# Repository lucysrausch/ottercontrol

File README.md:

# OtterControl
Hardware files for OtterControl BLDC motor controller.

## What is OtterControl?
OtterControl is a open source, open hardware DC / BLDC motor controller.
The basic idea was to make the well-known VESC (http://vedder.se/2015/01/vesc-open-source-esc/) even cheaper - making hoverboard-powered armchairs or crazycarts affordable.

While these 350W hoverboards motors are great and quiet affordable (only 40€ in Germany),
you need a powerful ESC to get them running. Until now, the only open ESC I'm aware of is the VESC - which is great and all, but with ~100-120€ per piece quiet expensive.
That's why I decided to save on some parts:

* Single-Chip Gatedrivers
* Mosfets in D2PAK package
* Chinese HV buck converter
* STM32f3 instead of f4: still powerful enough, and with more internal analog peripherals

The STM32f303 has lots of internal peripherals such as OpAmps, PGAs etc.
Using this chip reduces external components and system complexity - saving about 10€.
Also, using D2PAK Mosfets allows more flexible part selection - saving another 20€ with almost the same specs.

The final BOM for 50pcs of OtterControl turns out to be ~19€ per piece.

## Specs
* max. 50A continous motor current (~90A peak)
* max. 80V (with 63V capacitors = 14S LiIon)
* STMBL Codebase ("easy to use", configurable)
* no additional programming device (USB DFU support)

* UART, RS485, CAN, USB
* PPM (to be implemented)

* 3 GPIOs, sharing one Timer (eg. as hall sensor input, quadrature encoder)
* 5V max. 200mA out (eg. for hall sensors)
* Otter

## Versions

There are currently two different versions of OtterControl V1.3:
One with 1mOhm current-sensing shunts, and one with 3mOhm.
The reason for this:

To measure the phase current, the f303 internal PGA is set to 16x gain.
This gives a input range of 3.2AVDD / 16 = 200mV.
It is necessary to measure positiv and negative currents, so the shunt is pre-biased to 100mV, giving +/- 100mV measurable voltage drop.

* With 1mOhm, this means 100A full scale
* With 3mOhm, this means 33A full scale

Depending on your application, you want as much current resolution as possible.
For a 5A DC motor, or a small BLDC, 33A is way enough, archiving good current regulation.
However, for applications with more current, 1mOhm increases the current scale to the necessary range.

## Software

OtterControl is based on the stmbl codebase (https://github.com/rene-dev/stmbl).
A ported version can be found in my fork (ottercontrol branch).
Essentially, the code on the f303 is the same as in stmbl, but without the f4 this mcu now also handles encoder input, position regulation, user settings etc.

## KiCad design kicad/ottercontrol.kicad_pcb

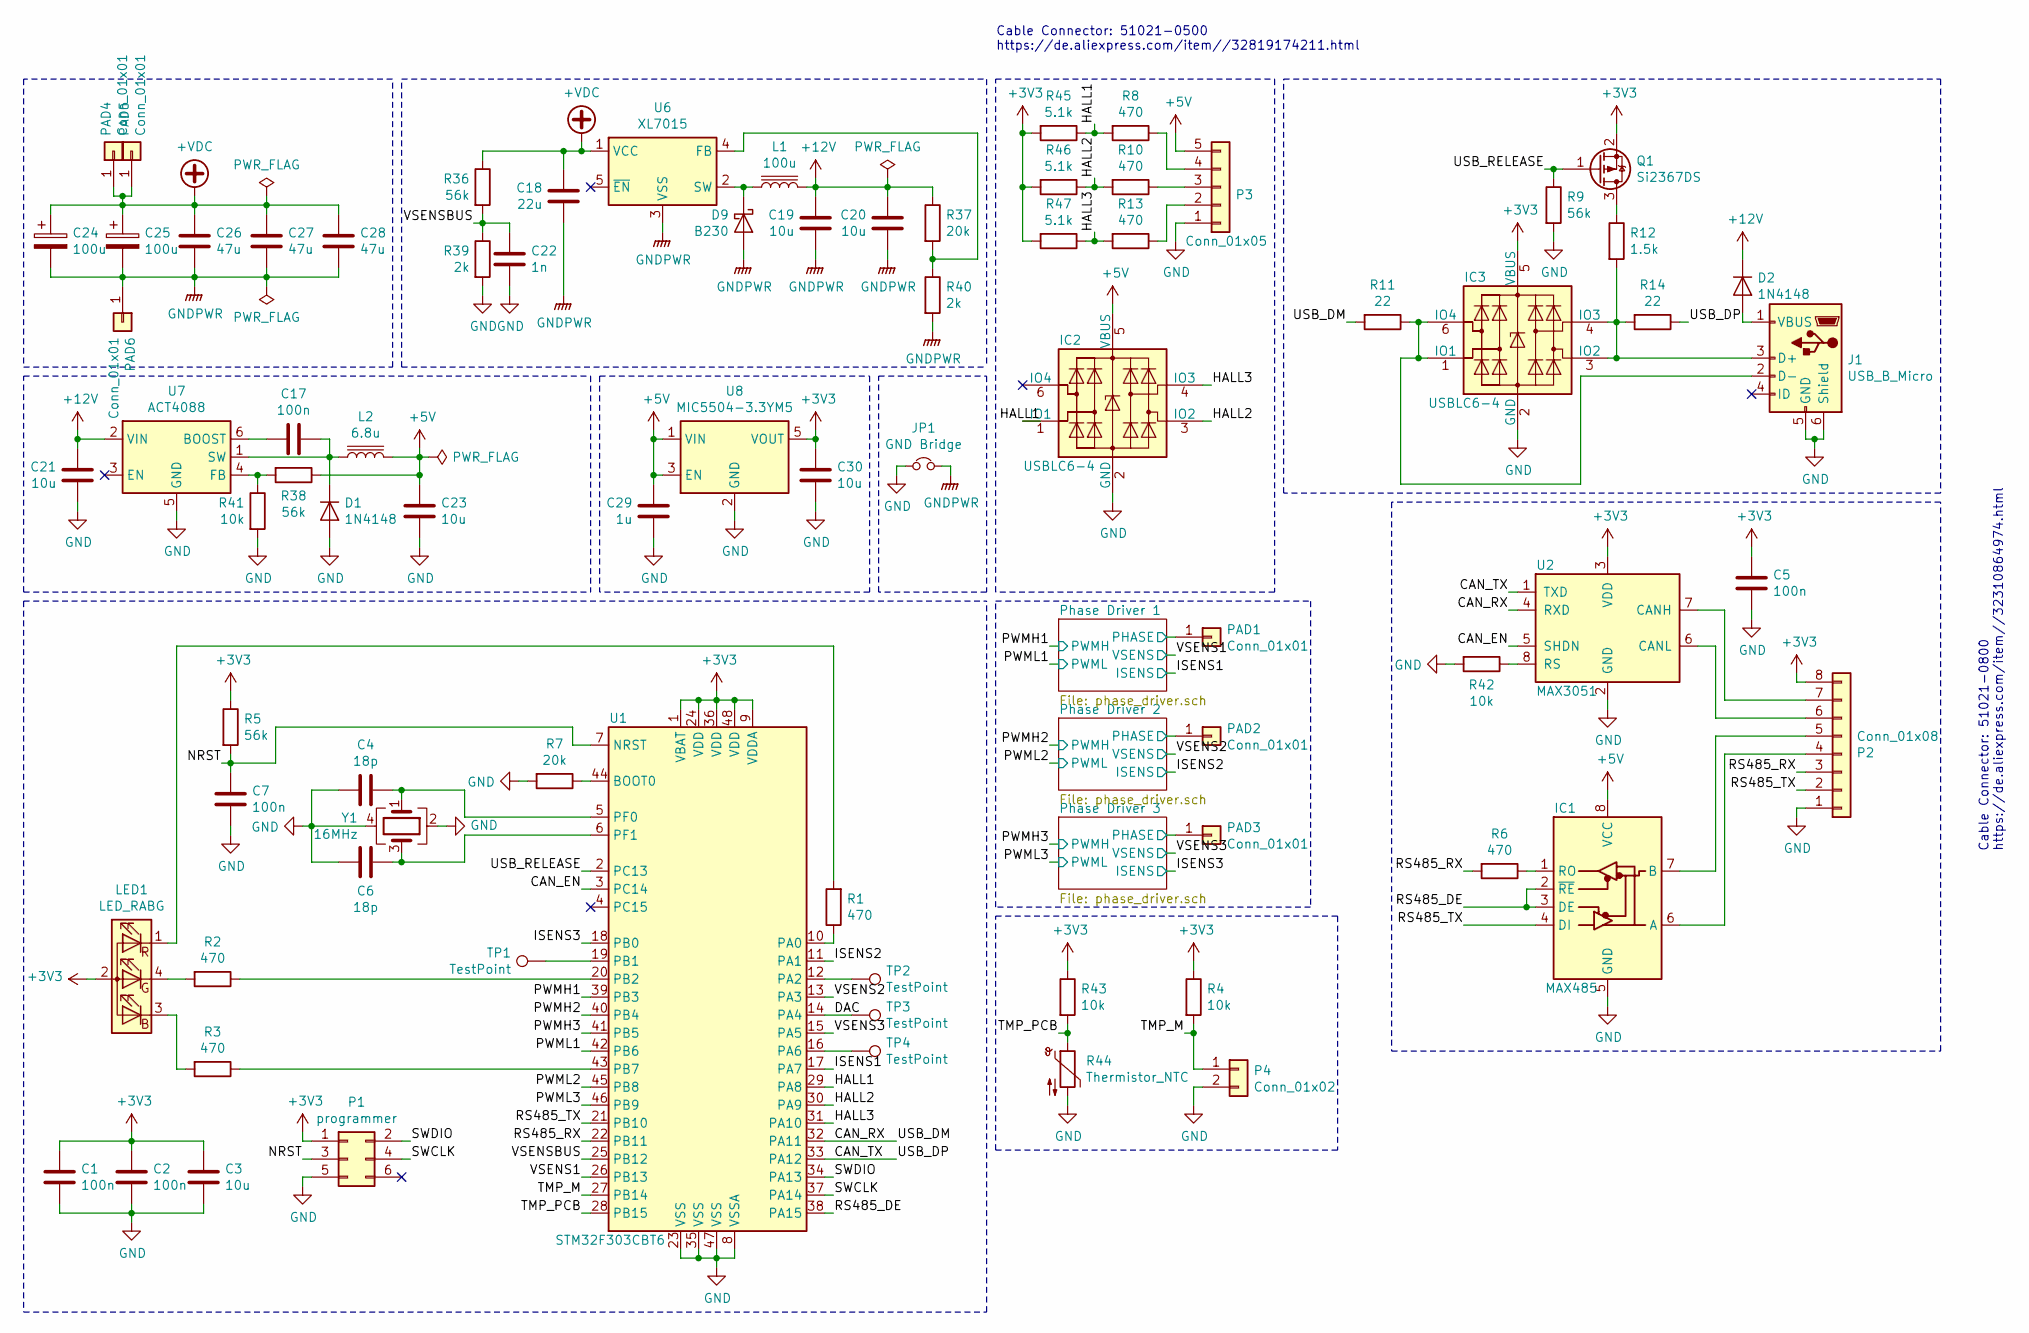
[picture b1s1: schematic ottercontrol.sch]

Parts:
C1, C2, C5, C7: 100n; C_0603_1608Metric; Voltage Rating DC 25; MPN GRM033C81E104KE14E
C3, C23, C30: 10u; C_0603_1608Metric; Voltage Rating DC 6.3; MPN JMK107ABJ106MA-T
C4, C6: 18p; C_0603_1608Metric; Tolerance 1%; MPN GRM0335C1E180FA01D
C17: 100n; C_0603_1608Metric; Voltage Rating DC 50; MPN CC0603MRY5V9BB104
C18: 22u; C_2220_5650Metric; Voltage Rating DC 100; MPN C5750X7R1E226M250KA
C19, C20, C21: 10u; C_1206_3216Metric; Voltage Rating DC 25; MPN TMK316BJ106KL-T
C22: 1n; C_0603_1608Metric; Voltage Rating DC 50; MPN 885012206083
C24, C25: 100u; CP_Radial_D12.5mm_P5.00mm; Voltage Rating DC 100; MPN 107CKS100MLQ
C26, C27, C28: 47u; C_2220_5650Metric; Voltage Rating DC 100; MPN CGA9N3X7R1E476M230KB
C29: 1u; C_0603_1608Metric; Voltage Rating DC 25; MPN 885012106022
D1, D2: 1N4148; D_SOD-323F; MPN 1N4148WS
D9: B230; D_SMA; MPN B230AE-13
IC1: MAX485; SOIC-8_3.9x4.9mm_P1.27mm; MPN MAX485CSA+
IC2, IC3: USBLC6-4; SOT-23-6; MPN USBLC6-4SC6
J1: USB_B_Micro; USB_Micro-B_Molex-105017-0001; MPN 105017-0001
JP1: GND Bridge; SolderJumper-2_P1.3mm_Bridged_Pad1.0x1.5mm; MPN n/a
L1: 100u; L_Coilcraft_LPS6235; MPN LPS6235-104MRC
L2: 6.8u; L_Coilcraft_LPS6235; MPN LPS6235-682MRC
LED1: LED_RABG; LED_Avago_PLCC4_3.2x2.8mm_CW
P1: programmer; Tag-Connect_TC2030-IDC-NL_2x03_P1.27mm_Vertical; MPN TC2030-MCP-NL
P2: Conn_01x08; Molex_PicoBlade_53261-0871_1x08-1MP_P1.25mm_Horizontal; MPN 53261-0871
P3: Conn_01x05; Molex_PicoBlade_53261-0571_1x05-1MP_P1.25mm_Horizontal; MPN 53261-0571
P4: Conn_01x02; PinHeader_1x02_P2.54mm_Vertical; MPN n/a
PAD1, PAD2, PAD3, PAD4, PAD5, PAD6: Conn_01x01; TestPoint_THTPad_4.0x4.0mm_Drill2.0mm; MPN n/a
Q1: Si2367DS; SOT-23; MPN SI2367DS-T1-GE3
R1, R2, R3, R6, R8, R10, R13: 470; R_0603_1608Metric; MPN RC0603FR-07100RL
R4, R41, R42, R43: 10k; R_0603_1608Metric; MPN RC0603FR-0710KL
R5, R9, R36, R38: 56k; R_0603_1608Metric; MPN RC0603FR-0756KL
R7, R37: 20k; R_0603_1608Metric; MPN RC0603FR-0720KL
R11, R14: 22; R_0603_1608Metric; MPN RC0603FR-0722RL
R12: 1.5k; R_0603_1608Metric; MPN RC0603FR-071K5L
R39, R40: 2k; R_0603_1608Metric; MPN RC0603FR-072KL
R44: Thermistor_NTC; R_0603_1608Metric; MPN 103AT
R45, R46, R47: 5.1k; R_0603_1608Metric; MPN RC0603FR-075K1L
TP1, TP2, TP3, TP4: TestPoint; TestPoint_Pad_D1.0mm; MPN n/a
U1: STM32F303CBT6; LQFP-48_7x7mm_P0.5mm; MPN STM32F303CBT6
U2: MAX3051; SOIC-8_3.9x4.9mm_P1.27mm; MPN MAX3051ESA+
U6: XL7015; TO-252-5_TabPin3; MPN XL7015
U7: ACT4088; TSOT-23-6; MPN ACT4088US-T
U8: MIC5504-3.3YM5; SOT-23-5; MPN MIC5504-3.3YM5-TR
Y1: 16MHz; Crystal_SMD_3225-4Pin_3.2x2.5mm; MPN FA-238 16.0000MB-K3

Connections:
+3V3: C1.1, C2.1, C3.1, C5.1, C30.1, IC3.5 (VBUS), LED1.2 (A), P1.1, P2.8, Q1.2 (S), R4.1, R5.1, R43.1, R45.2, R46.2, R47.2, U1.1 (VBAT), U1.9 (VDDA), U1.24 (VDD), U1.36 (VDD), U1.48 (VDD), U2.3 (VDD), U8.5 (VOUT); also elsewhere on the board
+5V: C23.1, C29.1, IC1.8 (VCC), IC2.5 (VBUS), L2.2, P3.5, R38.1, U8.1 (VIN), U8.3 (EN)
+12V: C19.1, C20.1, C21.1, D2.1 (K), L1.2, R37.1, U7.2 (VIN); also elsewhere on the board
+VDC: C18.1, C24.1, C25.1, C26.1, C27.1, C28.1, PAD4.1, PAD5.1, R36.1, U6.1 (VCC); also elsewhere on the board
/CAN_EN: U1.3 (PC14), U2.5 (SHDN)
/CAN_RX: R11.2, U1.32 (PA11), U2.4 (RXD)
/CAN_TX: R14.1, U1.33 (PA12), U2.1 (TXD)
/DAC: TP3.1, U1.14 (PA4)
/HALL1: IC2.1 (IO1), R8.2, R45.1, U1.29 (PA8)
/HALL2: IC2.3 (IO2), R10.2, R46.1, U1.30 (PA9)
/HALL3: IC2.4 (IO3), R13.2, R47.1, U1.31 (PA10)
/ISENS1: U1.17 (PA7); also elsewhere on the board
/ISENS2: U1.11 (PA1); also elsewhere on the board
/ISENS3: U1.18 (PB0); also elsewhere on the board
/NRST: C7.1, P1.3, R5.2, U1.7 (NRST)
/PWMH1: U1.39 (PB3); also elsewhere on the board
/PWMH2: U1.40 (PB4); also elsewhere on the board
/PWMH3: U1.41 (PB5); also elsewhere on the board
/PWML1: U1.42 (PB6); also elsewhere on the board
/PWML2: U1.45 (PB8); also elsewhere on the board
/PWML3: U1.46 (PB9); also elsewhere on the board
/Phase Driver 1/PHASE: PAD1.1; also elsewhere on the board
/Phase Driver 2/PHASE: PAD2.1; also elsewhere on the board
/Phase Driver 3/PHASE: PAD3.1; also elsewhere on the board
/RS485_DE: IC1.2 (~RE), IC1.3 (DE), U1.38 (PA15)
/RS485_RX: P2.3, R6.2, U1.22 (PB11)
/RS485_TX: IC1.4 (DI), P2.2, U1.21 (PB10)
/SWCLK: P1.4, U1.37 (PA14)
/SWDIO: P1.2, U1.34 (PA13)
/TMP_M: P4.1, R4.2, U1.27 (PB14)
/TMP_PCB: R43.2, R44.1, U1.28 (PB15)
/USB_RELEASE: Q1.1 (G), R9.1, U1.2 (PC13)
/VSENS1: U1.26 (PB13); also elsewhere on the board
/VSENS2: U1.13 (PA3); also elsewhere on the board
/VSENS3: U1.15 (PA5); also elsewhere on the board
/VSENSBUS: C22.1, R36.2, R39.1, U1.25 (PB12)
GND: C1.2, C2.2, C3.2, C4.2, C5.2, C6.2, C7.2, C21.2, C22.2, C23.2, C29.2, C30.2, D1.2 (A), IC1.5 (GND), IC2.2 (GND), IC3.2 (GND), J1.5 (GND), J1.6 (Shield), JP1.1, P1.5, P2.1, P3.1, P4.2, R7.2, R9.2, R39.2, R41.2, R42.2, R44.2, U1.8 (VSSA), U1.23 (VSS), U1.35 (VSS), U1.47 (VSS), U2.2 (GND), U7.5 (GND), U8.2 (GND), Y1.2, Y1.4; also elsewhere on the board
GNDPWR: C18.2, C19.2, C20.2, C24.2, C25.2, C26.2, C27.2, C28.2, D9.2 (A), JP1.2, PAD6.1, R40.2, U6.3 (VSS); also elsewhere on the board
unnamed: C4.1, U1.5 (PF0), Y1.1
unnamed: C6.1, U1.6 (PF1), Y1.3
unnamed: C17.1, D1.1 (K), L2.1, U7.1 (SW)
unnamed: C17.2, U7.6 (BOOST)
unnamed: D2.2 (A), J1.1 (VBUS)
unnamed: D9.1 (K), L1.1, U6.2 (SW)
unnamed: IC1.1 (RO), R6.1
unnamed: IC1.6 (A), P2.4
unnamed: IC1.7 (B), P2.5
unnamed: IC3.1 (IO1), IC3.6 (IO4), J1.2 (D-), R11.1
unnamed: IC3.3 (IO2), IC3.4 (IO3), J1.3 (D+), R12.2, R14.2
unnamed: LED1.1 (RK), R1.2
unnamed: LED1.3 (BK), R3.2
unnamed: LED1.4 (GK), R2.2
unnamed: P2.6, U2.6 (CANL)
unnamed: P2.7, U2.7 (CANH)
unnamed: P3.2, R13.1
unnamed: P3.3, R10.1
unnamed: P3.4, R8.1
unnamed: Q1.3 (D), R12.1
unnamed: R1.1, U1.10 (PA0)
unnamed: R2.1, U1.20 (PB2)
unnamed: R3.1, U1.43 (PB7)
unnamed: R7.1, U1.44 (BOOT0)
unnamed: R37.2, R40.1, U6.4 (FB)
unnamed: R38.2, R41.1, U7.4 (FB)
unnamed: R42.1, U2.8 (RS)
unnamed: TP1.1, U1.19 (PB1)
unnamed: TP2.1, U1.12 (PA2)
unnamed: TP4.1, U1.16 (PA6)

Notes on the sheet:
Cable Connector: 51021-0500 https://de.aliexpress.com/item//32819174211.html
Cable Connector: 51021-0800 https://de.aliexpress.com/item//32310864974.html

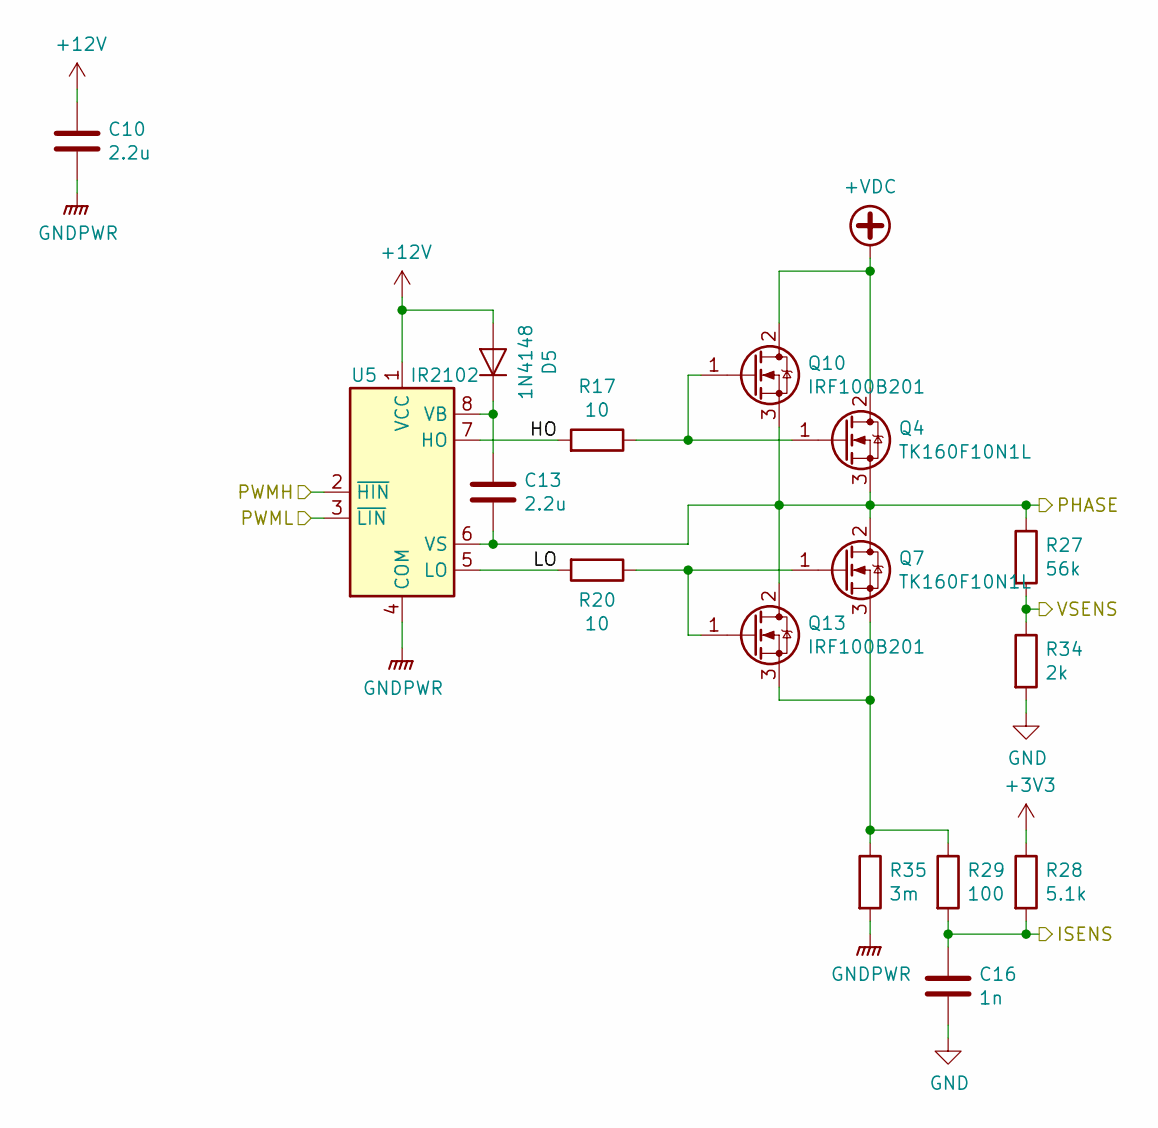
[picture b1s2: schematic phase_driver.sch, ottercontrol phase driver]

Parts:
C8, C11: 2.2u; C_0603_1608Metric; Voltage Rating DC 25; MPN GRM188R61E225MA12D
C14: 1n; C_0603_1608Metric; Voltage Rating DC 50; MPN 885012206083
D3: 1N4148; D_SOD-323F; MPN 1N4148WS
Q2, Q5: TK160F10N1L; TO-263-2; MPN TK160F10N1L,LQ
Q8, Q11: IRF100B201; TO-220-3_Vertical; MPN IRF100B201
R15, R18: 10; R_0603_1608Metric; MPN RC0603FR-0710RP
R21: 56k; R_0603_1608Metric; MPN RC0603FR-0756KL
R22: 5.1k; R_0603_1608Metric; MPN RC0603FR-075K1L
R23: 100; R_0603_1608Metric; MPN RC0603FR-07100RL
R30: 2k; R_0603_1608Metric; MPN RC0603FR-072KL
R31: 3m; R_2512_6332Metric; MPN WSLF25123L000FEA
U3: IR2102; SOIC-8_3.9x4.9mm_P1.27mm

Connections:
+3V3: R22.1; also elsewhere on the board
+12V: C8.1, D3.2 (A), U3.1 (VCC); also elsewhere on the board
+VDC: Q2.2 (D), Q8.2 (D); also elsewhere on the board
/ISENS1: C14.1, R22.2, R23.2; also elsewhere on the board
/PWMH1: U3.2 (~HIN); also elsewhere on the board
/PWML1: U3.3 (~LIN); also elsewhere on the board
/Phase Driver 1/HO: R15.2, U3.7 (HO)
/Phase Driver 1/LO: R18.2, U3.5 (LO)
/Phase Driver 1/PHASE: C11.2, Q2.3 (S), Q5.2 (D), Q8.3 (S), Q11.2 (D), R21.1, U3.6 (VS); also elsewhere on the board
/VSENS1: R21.2, R30.1; also elsewhere on the board
GND: C14.2, R30.2; also elsewhere on the board
GNDPWR: C8.2, R31.2, U3.4 (COM); also elsewhere on the board
unnamed: C11.1, D3.1 (K), U3.8 (VB)
unnamed: Q2.1 (G), Q8.1 (G), R15.1
unnamed: Q5.1 (G), Q11.1 (G), R18.1
unnamed: Q5.3 (S), Q11.3 (S), R23.1, R31.1

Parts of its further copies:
C9, C10, C12, C13: 2.2u; C_0603_1608Metric; Voltage Rating DC 25; MPN GRM188R61E225MA12D
C15, C16: 1n; C_0603_1608Metric; Voltage Rating DC 50; MPN 885012206083
D4, D5: 1N4148; D_SOD-323F; MPN 1N4148WS
Q3, Q4, Q6, Q7: TK160F10N1L; TO-263-2; MPN TK160F10N1L,LQ
Q9, Q10, Q12, Q13: IRF100B201; TO-220-3_Vertical; MPN IRF100B201
R16, R17, R19, R20: 10; R_0603_1608Metric; MPN RC0603FR-0710RP
R24, R27: 56k; R_0603_1608Metric; MPN RC0603FR-0756KL
R25, R28: 5.1k; R_0603_1608Metric; MPN RC0603FR-075K1L
R26, R29: 100; R_0603_1608Metric; MPN RC0603FR-07100RL
R32, R34: 2k; R_0603_1608Metric; MPN RC0603FR-072KL
R33, R35: 3m; R_2512_6332Metric; MPN WSLF25123L000FEA
U4, U5: IR2102; SOIC-8_3.9x4.9mm_P1.27mm

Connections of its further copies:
+3V3: R25.1, R28.1; also elsewhere on the board
+12V: C9.1, C10.1, D4.2 (A), D5.2 (A), U4.1 (VCC), U5.1 (VCC); also elsewhere on the board
+VDC: Q3.2 (D), Q4.2 (D), Q9.2 (D), Q10.2 (D); also elsewhere on the board
/ISENS2: C15.1, R25.2, R26.2; also elsewhere on the board
/ISENS3: C16.1, R28.2, R29.2; also elsewhere on the board
/PWMH2: U4.2 (~HIN); also elsewhere on the board
/PWMH3: U5.2 (~HIN); also elsewhere on the board
/PWML2: U4.3 (~LIN); also elsewhere on the board
/PWML3: U5.3 (~LIN); also elsewhere on the board
/Phase Driver 2/HO: R16.2, U4.7 (HO)
/Phase Driver 2/LO: R19.2, U4.5 (LO)
/Phase Driver 2/PHASE: C12.2, Q3.3 (S), Q6.2 (D), Q9.3 (S), Q12.2 (D), R24.1, U4.6 (VS); also elsewhere on the board
/Phase Driver 3/HO: R17.2, U5.7 (HO)
/Phase Driver 3/LO: R20.2, U5.5 (LO)
/Phase Driver 3/PHASE: C13.2, Q4.3 (S), Q7.2 (D), Q10.3 (S), Q13.2 (D), R27.1, U5.6 (VS); also elsewhere on the board
/VSENS2: R24.2, R32.1; also elsewhere on the board
/VSENS3: R27.2, R34.1; also elsewhere on the board
GND: C15.2, C16.2, R32.2, R34.2; also elsewhere on the board
GNDPWR: C9.2, C10.2, R33.2, R35.2, U4.4 (COM), U5.4 (COM); also elsewhere on the board
unnamed: C12.1, D4.1 (K), U4.8 (VB)
unnamed: C13.1, D5.1 (K), U5.8 (VB)
unnamed: Q3.1 (G), Q9.1 (G), R16.1
unnamed: Q4.1 (G), Q10.1 (G), R17.1
unnamed: Q6.1 (G), Q12.1 (G), R19.1
unnamed: Q6.3 (S), Q12.3 (S), R26.1, R33.1
unnamed: Q7.1 (G), Q13.1 (G), R20.1
unnamed: Q7.3 (S), Q13.3 (S), R29.1, R35.1

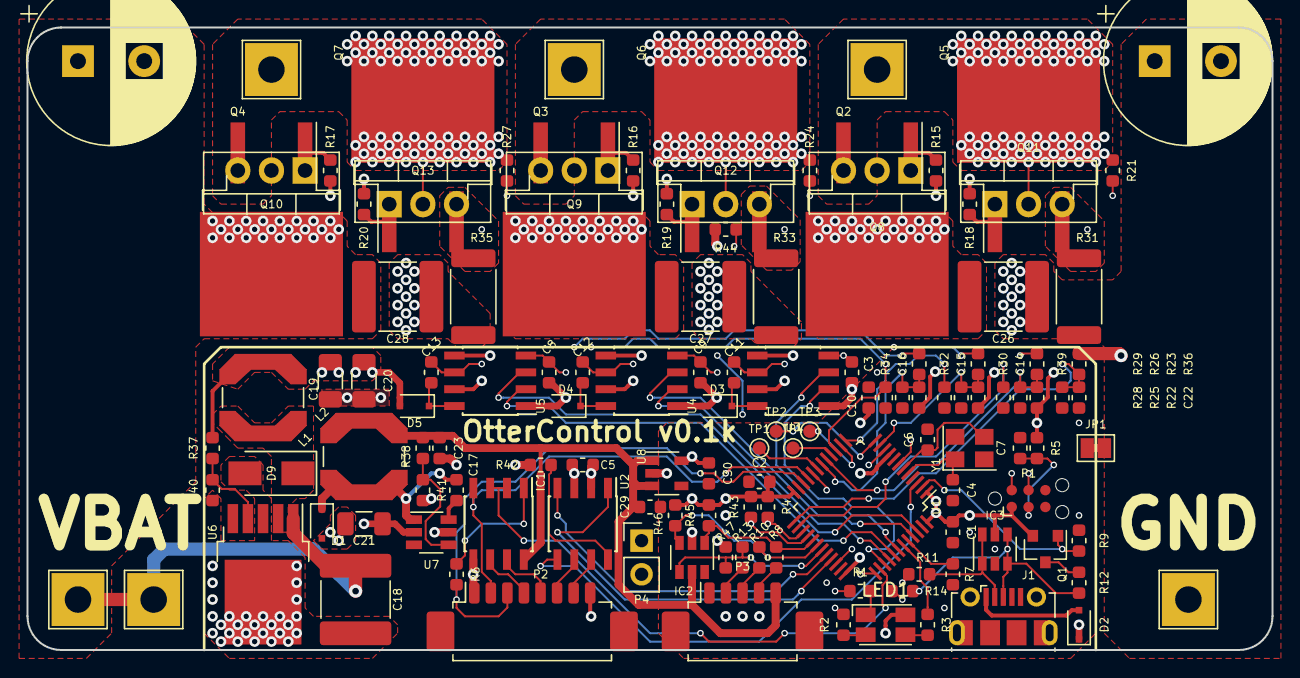
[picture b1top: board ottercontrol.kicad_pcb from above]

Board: 4 copper layers, 94.0 x 47.0 mm, 127 parts (0 on the bottom side), 86 nets.

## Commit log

2017-08-13 ADD: design files for ottercontrol V1.2
2017-08-15 UPD: final V1.2 design files
2019-01-03 added ignore for kicad files
2019-01-03 copied original schematic; places components on board
2019-01-05 placed and routed; preliminary finished
2019-01-05 added kicad 3D render
2019-01-06 made footprint fot mosfets hybrid for TO220 and D2PAK; added jumper instead of 0 Ohm resistor
2019-01-06 added look up table for MPNs
2019-01-06 added finished adding MPNs to all components
2019-01-06 exported PDF
2019-01-06 converted schemtic to png
2019-01-06 added pictures to README
2019-01-12 finalyzed design
2019-01-12 added new images
2019-01-12 minor changes
2019-01-12 put link to schematic at correct position in readme
2019-11-25 minor cosmetic modifications
2025-11-25 ADD: pcb pics
2025-11-25 renamed main
2025-11-25 Update README.md with pictures
